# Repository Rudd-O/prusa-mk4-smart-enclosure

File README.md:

# Prusa MK4 smart enclosure

This project contains files and information for the Prusa MK4 smart enclosure,
documented [in its own guide](https://rudd-o.com/smk4e).

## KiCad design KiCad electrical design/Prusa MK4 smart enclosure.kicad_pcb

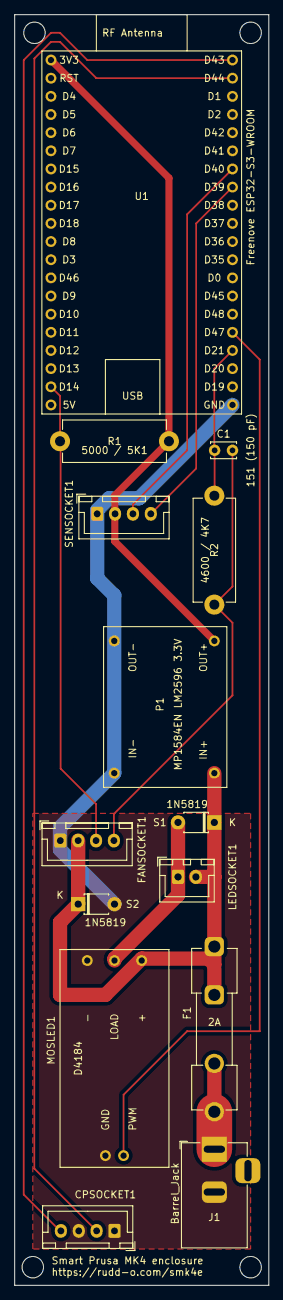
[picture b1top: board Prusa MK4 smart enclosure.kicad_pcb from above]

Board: 2 copper layers, 35.6 x 177.8 mm, 14 parts (0 on the bottom side), 13 nets.

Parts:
C1: 151 (150 pF); C_Disc_D3.4mm_W2.1mm_P2.50mm
CPSOCKET1: PINHD_1x4_Female; JST_XH_B4B-XH-A_1x04_P2.50mm_Vertical
F1: 2A; Fuseholder_Clip-5x20mm_Keystone_3517_Inline_P23.11x6.76mm_D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
FANSOCKET1: PINHD_1x4_Female; JST_XH_B4B-XH-A_1x04_P2.50mm_Vertical
J1: Barrel_Jack; BarrelJack_Horizontal
LEDSOCKET1: PINHD_1x2_Female; JST_XH_B2B-XH-A_1x02_P2.50mm_Vertical
MOSLED1: D4184; D4184 MOSFET control module
P1: MP1584EN LM2596 3.3V; MP1584EN LM2596
R1: 5000 / 5K1; R_Axial_DIN0614_L14.3mm_D5.7mm_P15.24mm_Horizontal
R2: 4600 / 4K7; R_Axial_DIN0614_L14.3mm_D5.7mm_P15.24mm_Horizontal
S1, S2: 1N5819; D_T-1_P5.08mm_Horizontal
SENSOCKET1: PINHD_1x4_Female; JST_XH_B4B-XH-A_1x04_P2.50mm_Vertical
U1: Freenove ESP32-S3-WROOM

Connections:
+3.3V: P1.3 (OUT), R1.2, SENSOCKET1.2, U1.2 (3V3)
+24V: F1.1, FANSOCKET1.2, LEDSOCKET1.2, MOSLED1.1 (+), P1.1 (IN), S1.1 (K), S2.1 (K)
GND: CPSOCKET1.1, CPSOCKET1.3, FANSOCKET1.1, J1.2, MOSLED1.3 (-), MOSLED1.5 (GND), P1.2 (GND), S2.2 (A), SENSOCKET1.1, U1.44 (GND)
unnamed: F1.2, J1.1
unnamed: MOSLED1.4 (PWM), U1.28 (GPIO47)
unnamed: SENSOCKET1.4, U1.36 (GPIO39/MTCK)
unnamed: SENSOCKET1.3, U1.37 (GPIO40/MTDO)
VDD: LEDSOCKET1.1, MOSLED1.2 (LOAD), S1.2 (A)
fan_pwm: C1.2, FANSOCKET1.4, R2.2
fan_pwm_filtered: C1.1, R2.1, U1.27 (GPIO21)
filt_toggle: CPSOCKET1.2, U1.42 (GPIO44/U0RXD)
led_toggle: CPSOCKET1.4, U1.43 (GPIO43/U0TXD)
pulse_counter: FANSOCKET1.3, R1.1, U1.20 (GPIO14/ADC2_CH3)

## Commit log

2024-04-30 Initial checkin of README.
2024-04-30 Add initial sketch.
2024-04-30 Add access point suggestion.
2024-04-30 Add license.
2024-04-30 Add to-do list.
2024-04-30 Gitignore added.
2024-04-30 Add KiCad files.
2024-04-30 Add 3MF and FreeCad files.
2024-04-30 Add todo item.
2024-05-01 Disable camera frame rate by default.
2024-05-01 Make camera react faster.
2024-05-04 Enable long-press for certain actions.
2024-05-04 Cover case of homeassistant sensor.
2024-07-03 Update prusa-mk4-smart-enclosure.yaml for 2024.6.6 ESPHome
    neffs' PR is still not merged, but it has been updated.
2024-07-24 Update to latest branch.
2024-09-03 Adapt to the latest ESPHome and pull request level.
2024-09-03 Add free heap sensor, commented.
2024-10-08 No longer necessary to include the patch for BME688.
2026-03-29 Version 1.1.

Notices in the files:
KiCad electrical design/Prusa MK4 smart enclosure.kicad_pcb:
License: https://creativecommons.org/licenses/by-nc/4.0
